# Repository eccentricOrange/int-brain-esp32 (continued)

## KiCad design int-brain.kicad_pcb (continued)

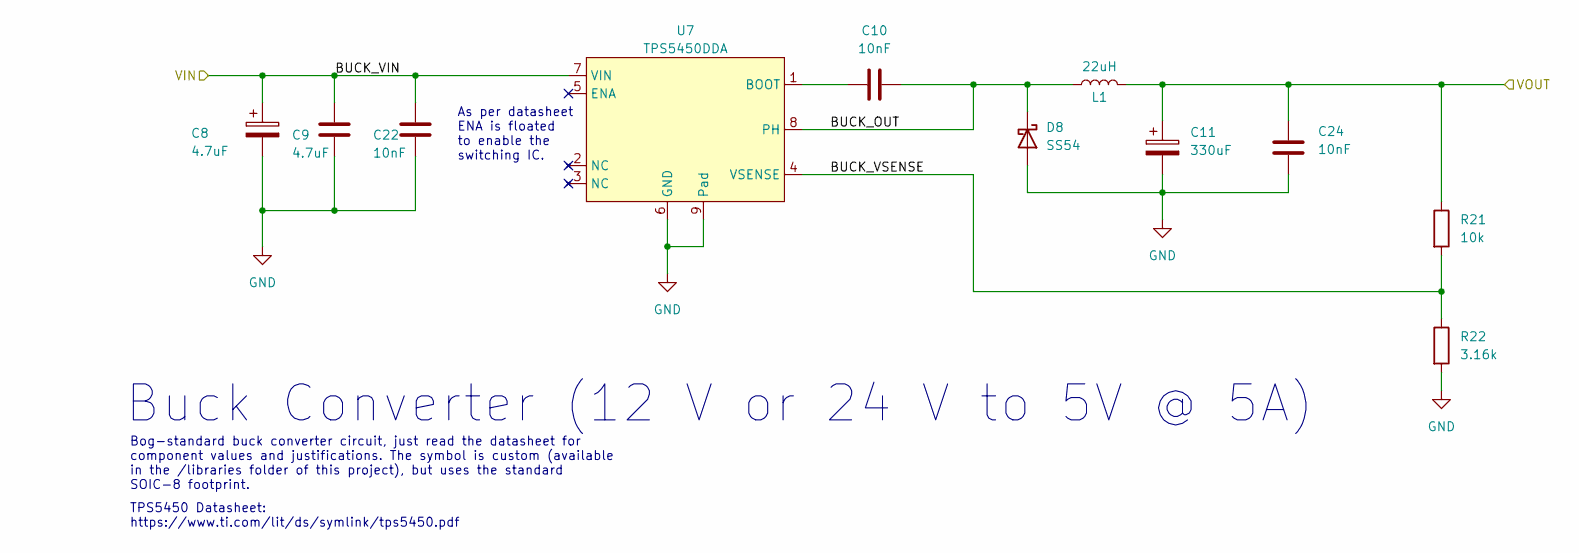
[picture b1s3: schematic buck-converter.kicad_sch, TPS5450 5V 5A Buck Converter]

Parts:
C8: 4.7uF; CP_Elec_4x5.4
C9: 4.7uF; C_0603_1608Metric_Pad1.08x0.95mm_HandSolder
C10: 10nF; C_0805_2012Metric_Pad1.18x1.45mm_HandSolder
C11: 330uF; CP_Elec_8x10.5
C22, C24: 10nF; C_0603_1608Metric_Pad1.08x0.95mm_HandSolder
D8: SS54; D_SMA_Handsoldering
L1: 22uH; L_10.4x10.4_H4.8
R21: 10k; R_1206_3216Metric_Pad1.30x1.75mm_HandSolder
R22: 3.16k; R_1206_3216Metric_Pad1.30x1.75mm_HandSolder
U7: TPS5450DDA; SOIC-8-1EP_3.9x4.9mm_P1.27mm_EP2.29x3mm_ThermalVias

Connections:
/buck1/BUCK_OUT: C10.2, D8.1 (K), L1.1, U7.8 (PH)
/buck1/BUCK_VSENSE: R21.2, R22.1, U7.4 (VSENSE)
GND: C8.2, C9.2, C11.2, C22.2, C24.2, D8.2 (A), R22.2, U7.6 (GND), U7.9 (Pad); also elsewhere on the board
unnamed: C10.1, U7.1 (BOOT)
VS: C8.1, C9.1, C22.1, U7.7 (VIN); also elsewhere on the board
VSS: C11.1, C24.1, L1.2, R21.1; also elsewhere on the board

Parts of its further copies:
C15: 4.7uF; CP_Elec_4x5.4
C16: 4.7uF; C_0603_1608Metric_Pad1.08x0.95mm_HandSolder
C17: 10nF; C_0805_2012Metric_Pad1.18x1.45mm_HandSolder
C18: 330uF; CP_Elec_8x10.5
C23, C25: 10nF; C_0603_1608Metric_Pad1.08x0.95mm_HandSolder
D9: SS54; D_SMA_Handsoldering
L2: 22uH; L_10.4x10.4_H4.8
R25: 10k; R_1206_3216Metric_Pad1.30x1.75mm_HandSolder
R26: 3.16k; R_1206_3216Metric_Pad1.30x1.75mm_HandSolder
U10: TPS5450DDA; SOIC-8-1EP_3.9x4.9mm_P1.27mm_EP2.29x3mm_ThermalVias

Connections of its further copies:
/buck2/BUCK_OUT: C17.2, D9.1 (K), L2.1, U10.8 (PH)
/buck2/BUCK_VIN: C15.1, C16.1, C23.1, U10.7 (VIN); also elsewhere on the board
/buck2/BUCK_VSENSE: R25.2, R26.1, U10.4 (VSENSE)
/buck2/VOUT: C18.1, C25.1, L2.2, R25.1; also elsewhere on the board
GND: C15.2, C16.2, C18.2, C23.2, C25.2, D9.2 (A), R26.2, U10.6 (GND), U10.9 (Pad); also elsewhere on the board
unnamed: C17.1, U10.1 (BOOT)

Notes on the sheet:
Buck Converter (12 V or 24 V to 5V @ 5A)
TPS5450 Datasheet: https://www.ti.com/lit/ds/symlink/tps5450.pdf
Bog-standard buck converter circuit, just read the datasheet for component values and justifications. The symbol is custom (available in the /libraries folder of this project), but uses the standard SOIC-8 footprint.
As per datasheet ENA is floated to enable the switching IC.

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
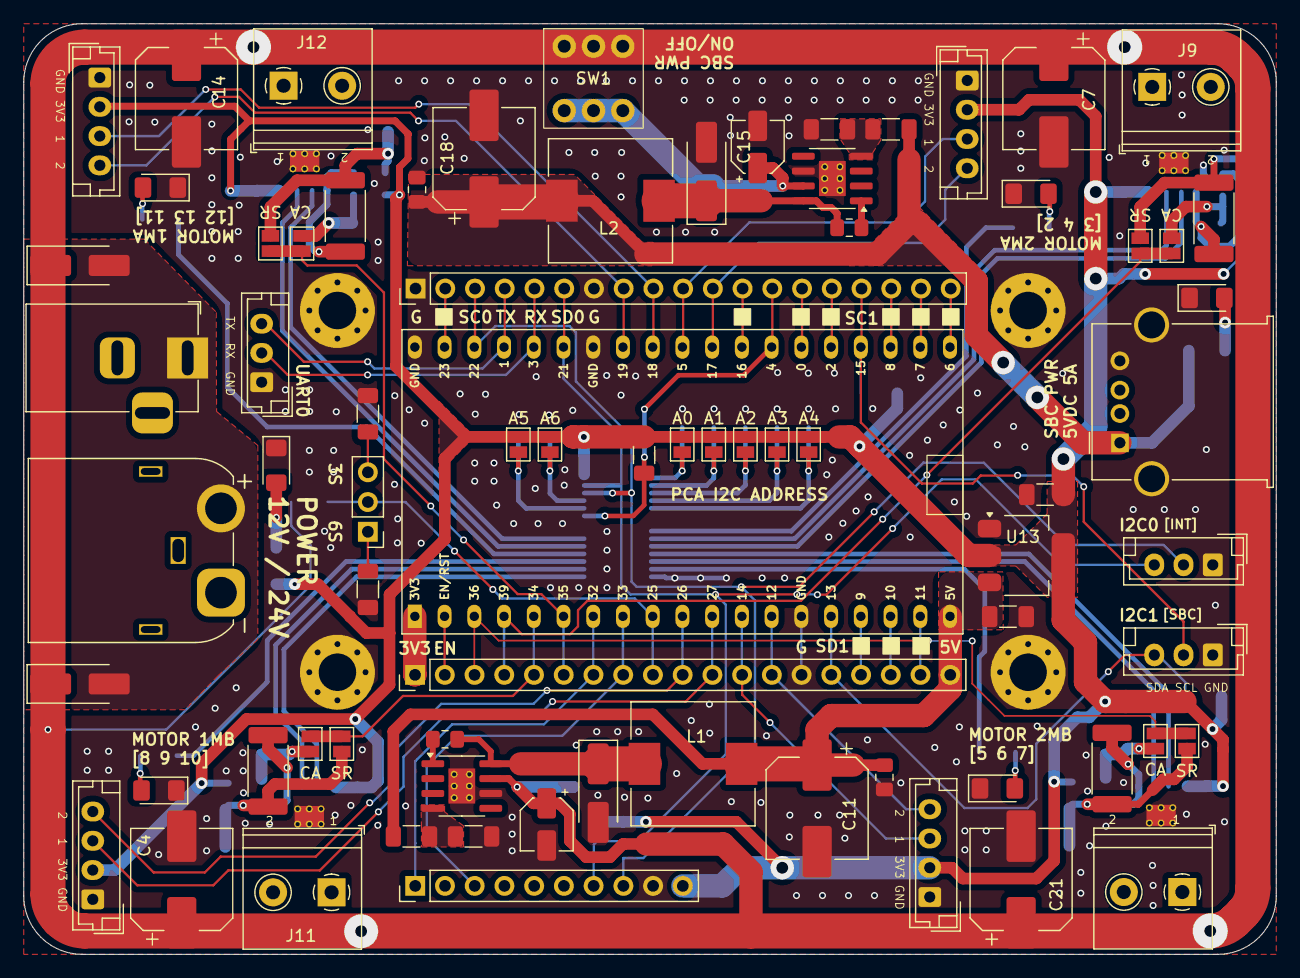
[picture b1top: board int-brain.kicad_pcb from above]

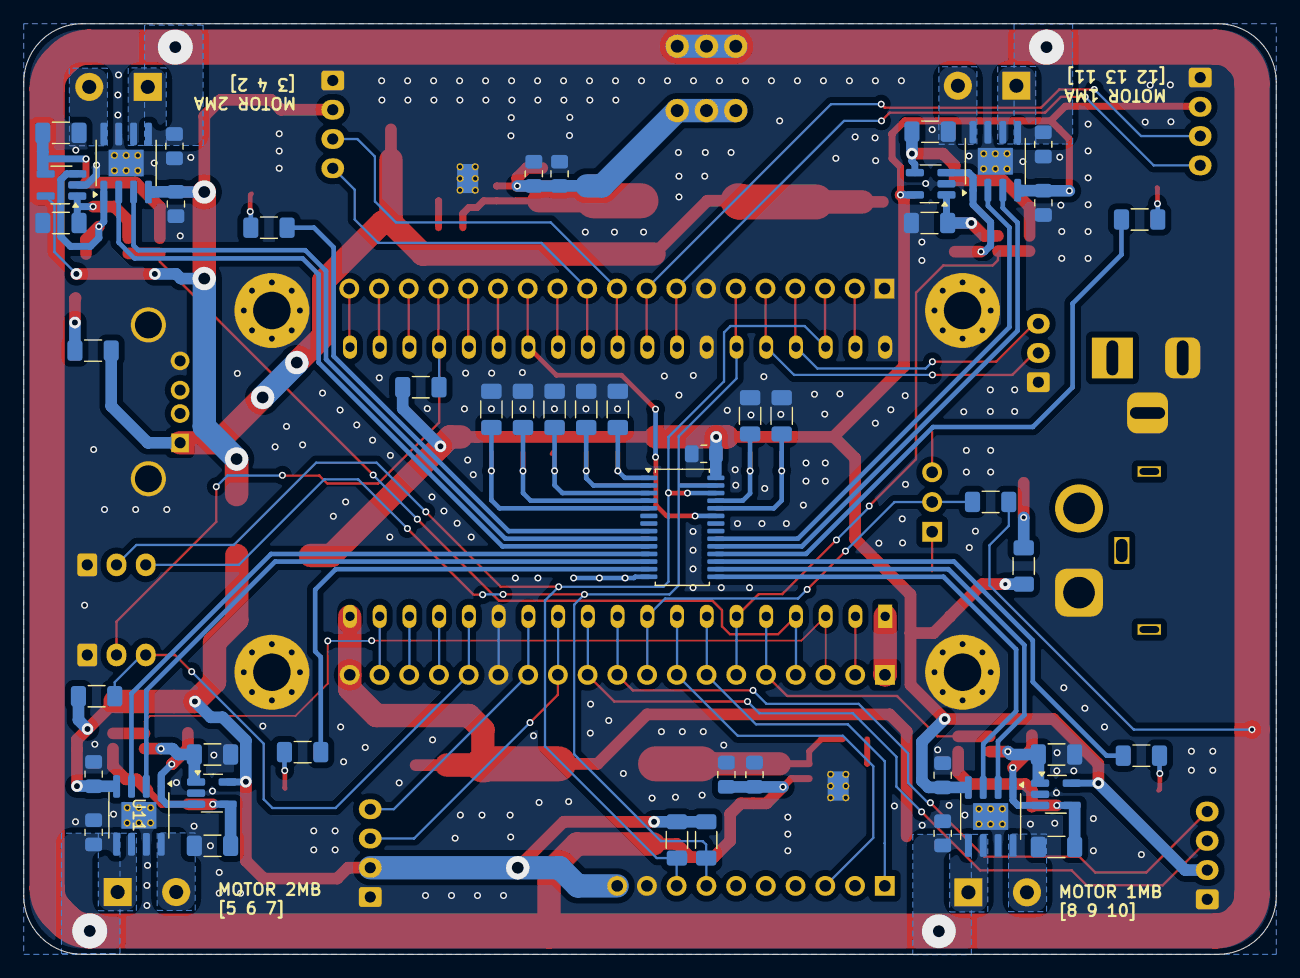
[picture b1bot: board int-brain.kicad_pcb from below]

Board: 2 copper layers, 107.0 x 79.5 mm, 127 parts (48 on the bottom side), 94 nets.

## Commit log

2024-05-31 fin sch, fin placement
2024-06-01 finish one iteration
2024-06-02 debug
2024-06-03 placed PCB components
2024-06-03 made smaller
2024-06-03 routing attempt
2024-06-04 small routing improvements
2024-06-04 re-do pinouts based on code
2024-06-04 finish schematic rearrangement
2024-06-04 finish?
2024-06-04 add formula
2024-06-05 set current sense resistors
2024-06-08 done placement
2024-06-08 done placement again
2024-06-09 done!?!?!
2024-06-09 add cap to PCA ic
2024-06-09 some zone
2024-06-09 add solder point for PCA I/O
2024-06-15 placed?
2024-06-16 traced
2024-06-16 done?
2024-06-16 minor improvements
2024-06-17 add pin-outs
2024-06-17 add LEDs
2024-06-17 link to README
2024-06-17 footprint updates
2024-06-19 change I2C and minor updates
2024-06-30 done
2024-07-02 basic redesign. PCB not up to date
2024-07-04 finally done?
2024-07-04 gpio update
2024-07-04 pull-ups
2024-07-30 something works
2024-07-31 worky!!!
2024-07-31 docs
2024-07-31 Create LICENSE
2024-07-31 update screenshots
2024-08-02 first commit?
2024-08-02 moved files
2024-08-02 idf version
2024-08-02 something?
2024-08-02 basic changes
2024-08-02 basic comments
2024-08-03 try something
2024-08-03 debug attempt
2024-08-03 bugfix
2024-08-03 oops
2024-08-03 clarify function types
2024-08-03 documentation
2024-08-04 new example
2024-08-05 magic numbers and constant names
2024-08-07 update for battery voltage?
2024-08-07 refactor attempt
2024-08-07 some small changes
2024-08-07 cmake?
2024-08-07 bugfixes
2024-08-07 worky?
2024-08-08 worky!
2024-08-08 re-organize
2024-08-17 read direct data
2024-09-01 add RPM measurement ability and direct example
2024-09-04 something
2024-09-22 overhauled for UART
2024-09-22 overhaul for UART
2024-10-05 and and and --> all
2024-12-07 merged pcb repo
2024-12-07 clean up
2024-12-07 rename folder
2024-12-07 fix readmes
2024-12-07 fix ignores
